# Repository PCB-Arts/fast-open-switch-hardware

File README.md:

The electronic design data from the KlusterLab 2.0 project is stored in this repo.

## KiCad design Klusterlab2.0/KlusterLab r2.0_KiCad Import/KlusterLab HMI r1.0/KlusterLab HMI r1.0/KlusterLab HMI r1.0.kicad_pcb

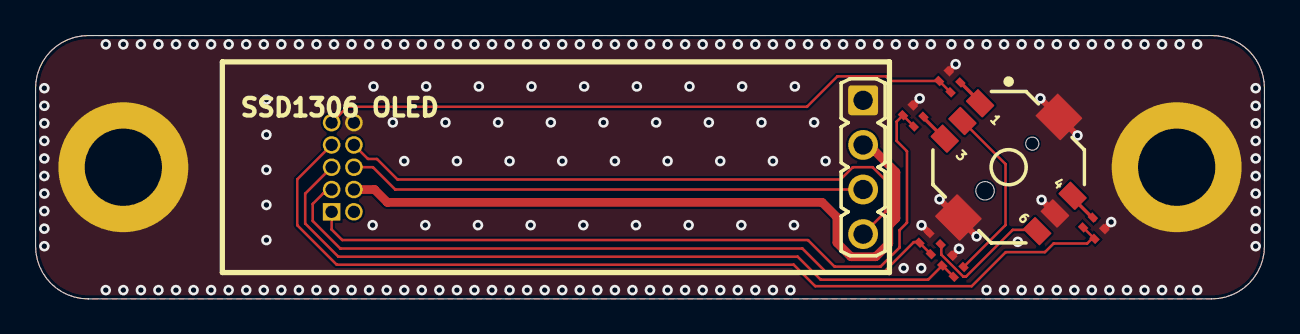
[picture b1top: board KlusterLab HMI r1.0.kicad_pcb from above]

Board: 2 copper layers, 70.0 x 15.0 mm, 15 parts (1 on the bottom side), 14 nets.

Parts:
C1, C2, C3, C4, C5: 100nF 50V; CAP_0402_L
J1: Pinheader, 10 Pin, THT, Straight; 62701021621
J2: WE / WR-PHD / 61300411121 / PinHeader / 1x4 Pin /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; WE_61300411121
M1, M2: 9774050360R
R1, R2, R3, R4, R5: 1k 1%; RES_0402_L
S1: AlpsAlpine SKRHACE010; AlpsAlpine_SKRHACE010

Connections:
Button_C: C4.1, J1.5, R4.1
Button_D: C5.1, J1.3, R5.1
Button_L: C2.1, J1.1, R2.1
Button_R: C3.1, J1.7, R3.1
Button_U: C1.1, J1.9, R1.1
GND: C1.2, C2.2, C3.2, C4.2, C5.2, J1.10, J2.1, M1.1, M2.1, S1.5, S1.MP1, S1.MP2
I2C_OLED_SCL: J1.6, J2.3
I2C_OLED_SDA: J1.8, J2.4
NetR1_2: R1.2, S1.1
NetR2_2: R2.2, S1.3
NetR3_2: R3.2, S1.4
NetR4_2: R4.2, S1.2
NetR5_2: R5.2, S1.6
VCC3V3: J1.4, J2.2

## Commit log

2025-07-16 Move verison 1.0 to dedicated folder
2025-07-17 Add Klusterlab version 2
